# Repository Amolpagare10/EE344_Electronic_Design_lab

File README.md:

<!-- Modify from here -->
# Project Overview    

### Project Name: *EcoSync 8X* - A dsPIC33A microcontroller based ultrasonic guided wave structural health monitoring system
### Team Number: TUE-08

### Team Members:  
(in alphabetical order)
- **[Amol Pagare](https://github.com/Amolpagare10)**
- **[Angad Singh](https://github.com/lightning-starboy)**  
- **[Anuj Gautam](https://github.com/10Anuj)**  
- **[Anuj Yadav](https://github.com/anujyadav10457)**  
- **[Subhanshu Choudhary](https://github.com/Subhanshu-Leo)**

## Problem Statement and Solution

This project introduces an **embedded data acquisition system** using **ultrasonic guided wave–based structural inspection**. The system is built around an **8-channel transducer interface**, where each channel can be dynamically configured as either a **transmitter** or **receiver**, enabling flexible and reconfigurable testing setups—all controlled via a user-friendly **graphical user interface (GUI)**.This is the device [User Manual.](others/USER_MANUAL.pdf)

---

### Key Features:

- **Signal Generation**: Produces a 100 kHz, 5-cycle Hanning-windowed pulse with a 10 V<sub>pp</sub> amplitude, which can be amplified up to 100 V<sub>pp</sub> using an external power amplifier.
- **Receiver Signal**: Includes high-fidelity signal acquisition with instrumentation amplifiers for accurate and noise-reduced signal capture.
- **Channel Multiplexing**: Supports 8-channel multiplexing for dynamic selection of transmitter and receiver transducers.
- **Wireless Communication**: Enables real-time data transmission to a host computer for visualization and offline analysis.
- **Structural Health Monitoring**: Ideal for applications in pipelines, metal and composite panels, and other critical infrastructure requiring long-term monitoring and inspection.
  <!--  -->

## 1. Source Code
### Project Directory Structure

```
/Project-Root
├── /src                      # Source code folder
│   ├── /dspic33ak128MC106      # Microcontroller 1
│   │   ├── integrated.c          # Handles DAC and ADC functionality
│   │   ├── command_protocol.c    # Implements the command protocol logic
│   │   ├── protocol_def.h        # Definitions for the command protocol
│   │
│   ├── /esp32                  # Microcontroller 2
│   │   ├── wifi_code.ino         # WiFi setup and communication code
```

### Programming the Microcontrollers

For programming the **dsPIC33AK128MC106** microcontroller, we used **MPLAB X IDE** in combination with the **XC-DSC compiler**.  
For the **ESP32** module, the programming was done using the **Arduino IDE**.  
In both cases, the code was written in the **C programming language**.

---

### How to Use the Code

### 1. Install Required Tools

- **MPLAB X IDE**: The official integrated development environment provided by Microchip for developing and debugging embedded applications.
- **XC-DSC Compiler**: A compiler specifically designed for 16-bit Digital Signal Controllers (DSCs) like the dsPIC33 series.

Both tools can be downloaded from the Microchip website:  
[https://www.microchip.com/en-us/tools-resources/develop/mplab-x-ide](https://www.microchip.com/en-us/tools-resources/develop/mplab-x-ide)

---

### 2. Creating a New Project in MPLAB X IDE

Once the tools are installed, follow these steps to create and configure a new project for the dsPIC33AK128MC106:

1. **Launch MPLAB X IDE**.
2. Go to the **File** menu and select **New Project**.
3. In the project wizard:
    - Select **Microchip Embedded** under **Categories**
    - Select **Application Projects** under **Projects**  
      
4. Click **Next**, then:
    - Choose **16-bit DSCs (dsPIC33)** from the **Family** dropdown
    - Select **dsPIC33AK128MC106** from the list of devices  
      
5. Click **Next**, then choose the **XC-DSC** compiler from the list of available compilers  
   
6. Provide a name for your project and choose a directory where it will be saved  

---

### 3. Adding Source Code Files

Once your project is set up:

1. In the **Projects** tab within MPLAB X IDE, navigate to the `Source Files` folder.
2. Copy and paste the provided `.c` and `.h` files into the `Source Files` directory.  

---

### 4. Building and Programming the Device

To compile and upload your code:

1. Click on the **Build Project** button (hammer icon) in the toolbar to compile the code.  
   
2. After a successful build, click the **Make and Program Device** button (downward arrow icon) to upload the code to the microcontroller.  
   
3. Once the microcontroller is programmed successfully, the onboard **status LED** should start blinking, indicating that the code is running.

---

## 2. PCB Design
```
/Project-Root
├──pcb/
|  ├── pictures/                         # Existing folder
|  ├── 1N914.zip                         # Diode library
|  ├── LIB_23LCV04M-I_ST.zip            # Official library
|  ├── LIB_DAC7821IPWR.zip              # Official DAC library
|  ├── MAX1426EAI_.zip                  # ADC or other component library
|  ├── Readme.md                        # Main documentation or instructions
|  ├── design.kicad_pcb                 # KiCAD PCB layout
|  ├── design.kicad_pro                 # KiCAD project file
|  ├── design.kicad_sch                 # KiCAD schematic file
|  ├── ul_DAC7821IPW.zip                # User-provided DAC library
|  ├── ul_INA128U.zip                   # User-provided instrumentation amp
|  ├── ul_TL072CP.zip                   # User-provided op-amp library
```
We've made our PCB using KiCAD software and these are the footprints used in the PCB design.

## 3. Laser Cut Panels
### Enclosure Design and Fabrication

The enclosure for our project was custom-designed and fabricated using **laser cutting**. All design files are located in the `/3d_models` directory. The box design was created using **Autodesk Fusion 360** and exported as a **DXF file** suitable for laser cutting.
```
/Project-Root
├── /3d_models              # 3D models and laser cut files
│   ├── box_model.dxf         # DXF file with all 6 faces for laser cutting
│   ├── Box_CAD_Sketch.png    # Sketch preview of the box design
```

### Box Details

- The enclosure consists of **six interlocking acrylic panels**, each precisely designed with **notches** that fit into complementary notches on adjacent panels for seamless assembly.
- Panels are cut from **5 mm thick acrylic sheets**.
- The box is assembled using **hot glue**, which securely holds the panels together.

---

### Custom Cutouts

- **Back Panel**:
  - Includes a cutout for the **power supply**.
- **Side Panel**:
  - It has a cutout specifically for the **dsPIC33AK128MC106 microcontroller board**.
  - Below the microcontroller cutout, there are **eight holes** for the **transducer connectors**, allowing easy interfacing with the external sensors.

## 4. Bill Of Materials  
This project involves various electronic components including microcontrollers, converters, sensors, and support modules, sourced from vendors like DigiKey, Robu, Mouser, and Microchip.

### Component Overview

| **Category**               | **Component**                             | **Quantity** | **Vendor**              | **Cost (INR)** |
|---------------------------|-------------------------------------------|--------------|--------------------------|----------------|
| **Microcontrollers & Dev Boards** | ESP32 WiFi Module, DIM Module, Development Board | 3            | DigiKey, Microchip       | ₹9,457.00      |
| **Signal Conversion**     | DAC, ADC, INA128                          | 3            | Mouser, DigiKey, Robu    | ₹1,910.00      |
| **Power Modules**         | SMPS (x2), Buck & Boost Converters       | 5            | DigiKey, Robu            | ₹4,420.00      |
| **Sensors**               | PZT Sensor (SP-5H)                        | 8            | CPS Lab                  | ₹40,000.00     |
| **Misc ICs**              | MUX, Electronic Switch, Opamp            | 3            | Mouser, DigiKey, Robu    | ₹2,675.00      |
| **Mechanical**            | Acrylic Sheet Panels (Laser Cut)         | 6            | WEL                      | NA             |

---

### **Total Cost**: ₹58,462.00

> Note: Cost for acrylic sheets not included.

## **Learning, Experiences, Hardships, and Difficulties Encountered**

<!-- This course has been a valuable learning experience for us. It taught us how to transform an idea into a tangible product, which was both challenging and exciting. Throughout the project, we experienced highs when things were progressing smoothly, when our DAC wasn't giveing the correct waveform, as well as lows when nothing seemed to work despite our efforts, when our ADC couldnt't work reliably. There were moments of frustration, especially when technical setbacks slowed us down or when not all team members could contribute equally due to other academic commitments, even when we had quizes and exam, we tried to invest some time according to our free timings. In hindsight, we believe a more effective distribution of tasks could have helped us manage these challenges better. Nonetheless, the journey was immensely enriching, and we’re grateful for the opportunity to learn and grow through this experience. -->

This course has been a valuable learning experience for us. It taught us how to transform an idea into a tangible product, which was both challenging and exciting. 

Throughout the project, we experienced several highs—such as when things were progressing smoothly—and lows, like when our DAC wasn't giving the correct waveform or when our ADC couldn’t work reliably. 

There were moments of frustration, especially when technical setbacks slowed us down or when not all team members could contribute equally due to other academic commitments. Even during quizzes and exams, we tried to invest time according to our free schedules.

In hindsight, we believe a more effective distribution of tasks could have helped us manage these challenges better. Nonetheless, the journey was immensely enriching, and we’re grateful for the opportunity to learn and grow through this experience.

## Current status and Future Prospects for our Project

---

### 1. Partially Incomplete ADC

#### What Was Done:
- Tested the ADC on the PCB using waveform inputs from the INA.
- Output signal remained constant across tests.
- Tried using an earlier-working ADC on a breadboard—still observed a constant output.

#### Unresolved Issues:
The root cause remains unidentified. Potential issues could include:
- Incorrect voltage reference.
- INA output entering saturation.
- Firmware misconfiguration.
- Inaccurate or missing clock signals.

#### Parts Not Completed:
- Full integration of the ADC into the signal chain.
- Validation using real digitized sensor data.
- Establishing a complete end-to-end data acquisition pipeline for signal processing.

---

### 2. Partially Incomplete Wi-Fi Module Interface

#### What Was Done:
- Attempted UART-based interfacing of the Wi-Fi module with the Curiosity board.
- Identified that the UART pins on the board were non-functional.

#### Progress Made:
- Successfully interfaced the Wi-Fi module with a GUI.
- Enabled both data transmission and reception.
- Initially received garbage data when connected to a laptop, resolved by:
  - Splitting the code into two modules:
    - One for the Wi-Fi module at **115200 baud rate**.
    - One for laptop communication at **9600 baud rate**.

#### Parts Not Completed:
- Wi-Fi integration with the Curiosity board.
- Wireless transmission of sensor data from the MCU.
- Real-time wireless data logging and remote visualization.

---

## Future Prospects

### 1. Enhanced GUI Interface
- Develop a more intuitive and interactive GUI.
- Key features to include:
  - Real-time waveform plotting.
  - Diagnostic alerts for system anomalies.
  - Interactive signal control and parameter tuning.

### 2. DI Map Algorithm Improvements
- Optimize the **Damage Index (DI)** mapping algorithm for better defect localization and embedded performance.
- Add a validation metric to evaluate and improve accuracy.
- Enable dynamic updates on the GUI for visual feedback.

### 3. Complete Wi-Fi Module Integration
- Finalize integration of the Wi-Fi module with the Curiosity board.
- Support seamless, real-time wireless data transmission.
- Enable remote monitoring through a web interface or mobile application.

### 4. SRAM-Based Memory Expansion
- Integrate external **SRAM** to overcome microcontroller memory limitations.
- Support:
  - High-resolution signal logging.
  - Buffered data acquisition.
  - Advanced signal processing tasks on-device.

---

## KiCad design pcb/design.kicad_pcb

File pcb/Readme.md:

# PCB Design Issues:

- Our SMD INA on the PCB was not working. We replaced it with another SMD INA, but it still didn't work. Since we didn’t have any more SMD INAs, we used a DIP INA on a breadboard and connected it to the PCB — and it started working.

- In the ADC, we grounded the CMLP pin (pin 11), as the datasheet mentioned that for DC coupling, it should be grounded. However, during breadboard testing, we found that it worked when connected to 5V instead.

- Even after all this, the ADC on the PCB is still not working. We tried to figure out the issue by checking if the clock is working, if we are receiving data at the ADC, and if the power supply to the ADC is correct. We found that everything appears to be in order, yet we are still not receiving any data from the ADC.

# Purpose of the PCB:

- In our project, almost everything relied on the PCB. We had to use components like the DAC, TL072, power amplifier, electronic switch, multiplexer, INA, and ADC — all of which required reliable and organized connections. Using a PCB was the best choice to ensure clean and consistent wiring.

- Moreover, we found that small mistakes on the breadboard made debugging very cumbersome. In contrast, the PCB allowed us to make all the connections properly and verify them once. After the PCB arrived and we tested it, we could trust the setup and focus on the actual performance of the circuit.

# Explanation of PCB connections 

- Our microcontroller was connected to the DAC to convert digital data into analog signals. The signal was then passed through a TL072 and a power amplifier to amplify it. Next, an electronic switch was used to select which transducer would transmit the signal.

- After transmission, a multiplexer (MUX) was used to select the transducer that would receive the signal. The received signal was then passed through an INA and a clipper — the INA amplified the signal, while the clipper limited high voltages to protect the circuit.

- Finally, the processed analog signal was fed into an ADC to convert it back into digital form, which was then sent to the PC for post-processing.

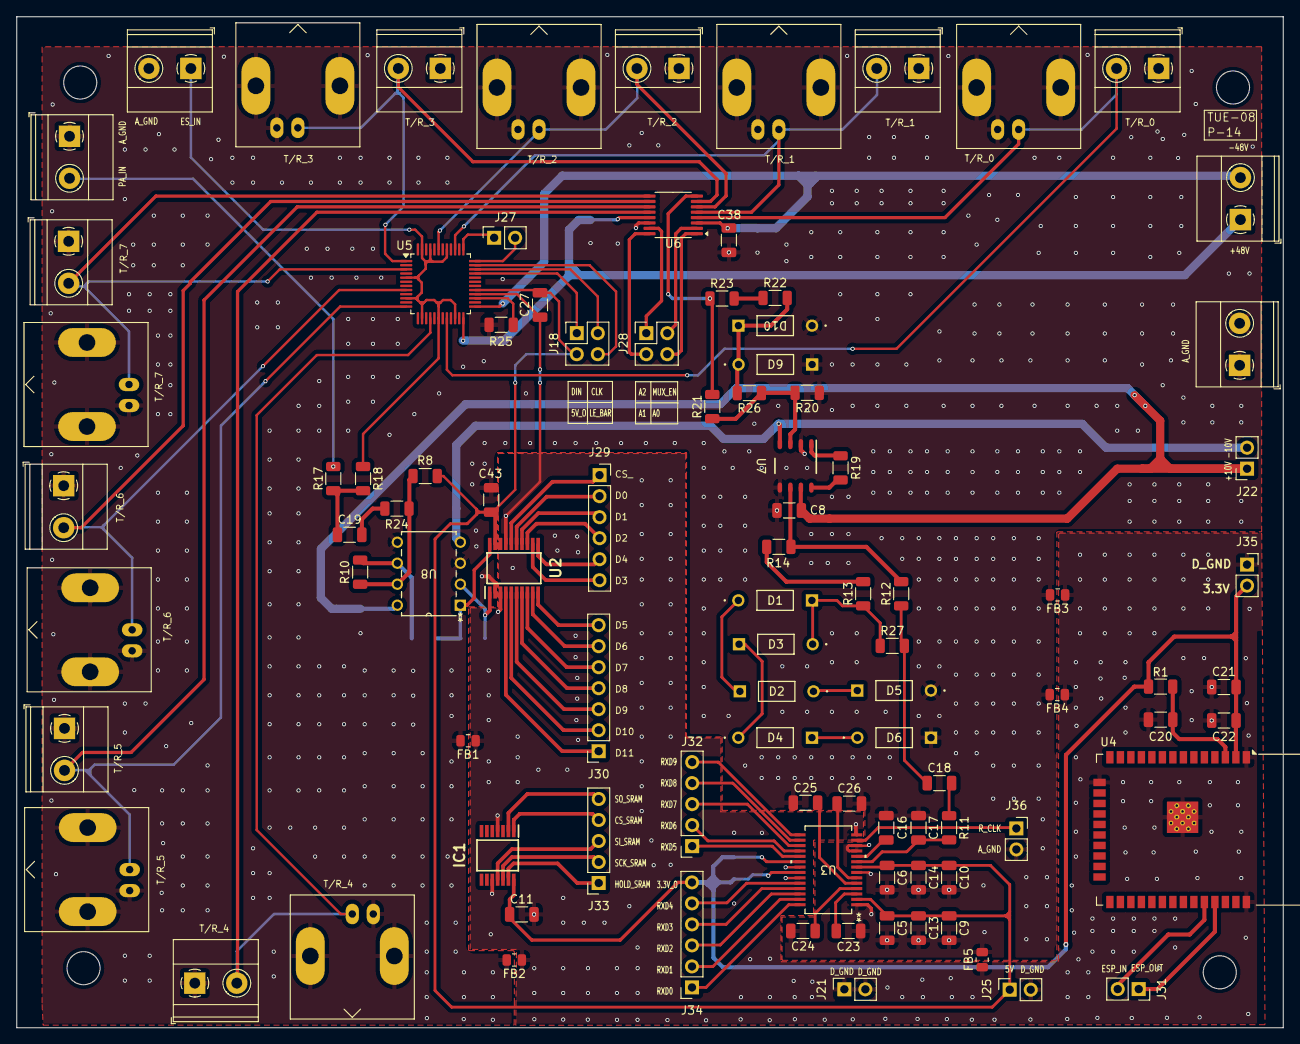
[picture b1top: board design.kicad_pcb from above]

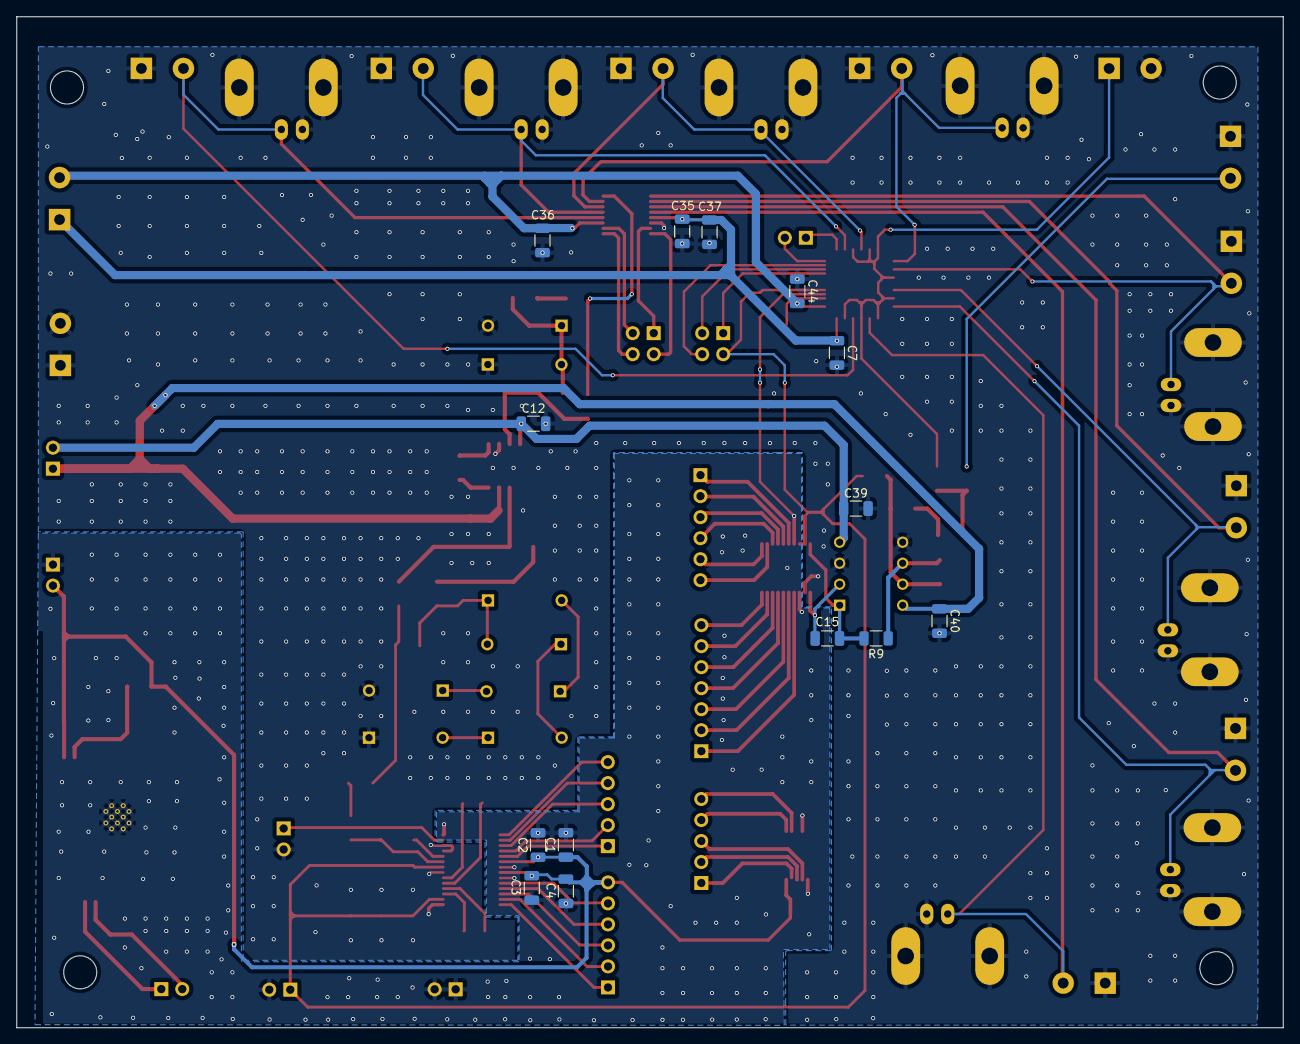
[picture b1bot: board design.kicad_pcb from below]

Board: 2 copper layers, 153.2 x 122.3 mm, 109 parts (14 on the bottom side), 87 nets.

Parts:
A_GND: Screw_Terminal_01x02; TerminalBlock_Phoenix_MKDS-1,5-2-5.08_1x02_P5.08mm_Horizont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
C1, C3, C13, C14: 2.2uf; C_1206_3216Metric
C2, C4, C8, C9, C10, C11, C12, C16, C18, C19, C23, C24, C25, C26, C27, C39, C40, C43, C44: 0.1uf; C_1206_3216Metric
C5, C6: 100pf; C_1206_3216Metric
C7, C37, C38: 0.1u; C_1206_3216Metric
C15: C; C_1206_3216Metric
C17: 22fp; C_1206_3216Metric
C20, C22: 0.1uF; C_1206_3216Metric
C21: 10uF; C_1206_3216Metric
C35, C36: 1u; C_1206_3216Metric
D1, D2, D3, D4, D5, D6, D9, D10: D; 1n914
FB1, FB2, FB3, FB4, FB5: FerriteBead; R_0805_2012Metric
IC1: 23LCV04M-I_ST; SOP65P640X120-14N
J2, J3, J4, J5, J6, J7, J8, J9: Conn_Coaxial; BNC_Amphenol_B6252HB-NPP3G-50_Horizontal
J10, J11, J12, J13, J14, J15, J16, J17, J19, J20, J23: Screw_Terminal_01x02; TerminalBlock_Phoenix_MKDS-1,5-2-5.08_1x02_P5.08mm_Horizont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
J18, J28: Conn_02x02_Top_Bottom; PinSocket_2x02_P2.54mm_Vertical
J21, J22, J25, J27, J31, J35, J36: Conn_01x02; PinSocket_1x02_P2.54mm_Vertical
J29, J34: Conn_01x06; PinSocket_1x06_P2.54mm_Vertical
J30: Conn_01x07; PinSocket_1x07_P2.54mm_Vertical
J32, J33: Conn_01x05; PinSocket_1x05_P2.54mm_Vertical
R1, R8, R10, R20: 10k; R_1206_3216Metric
R9: 5k; R_1206_3216Metric
R11: 50; R_1206_3216Metric
R12, R14, R17, R18, R21, R23, R25, R26, R27: 0; R_1206_3216Metric
R13, R19, R22: 100; R_1206_3216Metric
R24: 180; R_1206_3216Metric
U2: DAC7821IPWR; SOP65P640X120-20N
U3: MAX1426EAI+; adc
U4: ESP32-WROOM-32DM113DH6400PH3Q0; ESP32-WROOM-32D
U5: HV232FG-G; LQFP-48_7x7mm_P0.5mm
U6: TMUX8108PWR; TSSOP-16_4.4x5mm_P0.65mm
U7: INA128PA; ina128
U8: TL072CP; tl072

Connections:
+3.3V: C1.1, C2.1, C3.1, C4.1, C11.1, C21.2, C22.2, IC1.14 (VCC), J34.6, J35.2, R1.2, U3.20 (DVDD), U3.22 (DVDD), U4.2 (3V3)
+5V: C5.1, C6.1, C9.1, C10.1, C13.1, C14.1, C27.2, C43.2, J18.2, J25.1, R8.1, U2.18 (VDD), U2.19 (VREF), U3.2 (AVDD), U3.8 (AVDD), U5.29 (VDD)
+10V: C8.2, C40.1, J22.1, U7.7 (V+), U8.8 (VCC+)
+48V: C7.1, C35.1, C37.1, J23.1, U5.24 (VPP), U6.13 (VDD)
-10V: C12.1, C39.1, J22.2, U7.4 (V-), U8.4 (VCC-)
-48V: C36.2, C38.2, C44.2, J23.2, U5.25 (VNN), U6.3 (VSS)
A0: J28.4, U6.1 (A0)
A1: J28.2, U6.16 (A1)
A2: J28.1, U6.15 (A2)
A_GND: A_GND.1, C5.2, C6.2, C7.2, C8.1, C9.2, C10.2, C12.2, C13.2, C14.2, C16.1, C17.2, C23.2, C24.2, C25.2, C26.2, C35.2, C36.1, C37.2, C38.1, C39.2, C40.2, C43.1, C44.1, D5.1 (K), D6.2 (A), D9.2 (A), D10.1 (K), FB1.2, FB2.2, FB3.2, FB4.2, FB5.2, J2.2 (Ext), J3.2 (Ext), J4.2 (Ext), J5.2 (Ext), J6.2 (Ext), J7.2 (Ext), J8.2 (Ext), J9.2 (Ext), J10.1, J11.1, J12.1, J13.1, J14.1, J15.1, J16.1, J17.1, J19.1, J19.2, J20.2, J36.2, R20.1, R25.2, U2.2 (IOUT2), U3.1 (AGND), U3.7 (AGND), U3.11 (CMLP), U3.12 (CMLN), U6.14 (GND), U7.2 (V-IN), U7.5 (REF), U8.3 (1IN+), U8.5 (2IN+)
CLK: J18.3, U5.34 (CLK)
CLR: J27.2, U5.36 (CLR)
CS_: J29.1, U2.16 (CS_N)
CS_SRAM: IC1.1 (~CS), J33.4
D0: J29.2, U2.15 (DB0_LSB)
D1: J29.3, U2.14 (DB1)
D2: J29.4, U2.13 (DB2)
D3: J29.6, U2.12 (DB3)
D4: J29.5, U2.11 (DB4)
D5: J30.7, U2.10 (DB5)
D6: J30.6, U2.9 (DB6)
D7: J30.5, U2.8 (DB7)
D8: J30.4, U2.7 (DB8)
D9: J30.3, U2.6 (DB9)
D10: J30.2, U2.5 (DB10)
D11: J30.1, U2.4 (DB11_MSB)
DAC_OUT: C19.1, R17.2, R18.2
DIN: J18.1, U5.33 (DIN)
DOUT: J27.1, U5.37 (DOUT)
D_GND: C1.2, C2.2, C3.2, C4.2, C11.2, C20.1, C21.1, C22.1, C27.1, FB1.1, FB2.1, FB3.1, FB4.1, FB5.1, IC1.4 (VSS), IC1.10 (VBAT), J21.1, J21.2, J25.2, J35.1, U2.3 (GND), U2.17 (R_W_N), U3.14 (*OE/PD), U3.21 (DGND), U3.23 (DGND), U4.1 (GND), U4.15 (GND), U4.38 (GND), U4.39 (GND), U5.28 (GND)
ESP_DATA_IN: J31.2, U4.34 (RXD0)
ESP_DATA_OUT: J31.1, U4.35 (TXD0)
ES_IN: J20.1, R18.1, U5.5 (SW4), U5.10 (SW3), U5.14 (SW2), U5.18 (SW1), U5.22 (SW0), U5.41 (SW7), U5.45 (SW6), U5.47 (SW5)
HOLD_SRAM: IC1.13 (~HOLD/SIO3), J33.1
INA_OUT: C18.1, R12.1, R27.2
INN: C16.2, U3.10 (INN)
INP: C17.1, R11.2, U3.9 (INP)
LE_BAR: J18.4, U5.35 (*LE)
MUX_EN: J28.3, U6.2 (EN)
MUX_OUT: R21.2, R23.2, U6.8 (D)
unnamed: C18.2, R11.1
unnamed: C19.2, R24.2
unnamed: D1.2 (A), D3.1 (K), R13.1, R27.1
unnamed: D1.1 (K), D2.2 (A)
unnamed: D2.1 (K), D5.2 (A)
unnamed: D3.2 (A), D4.1 (K)
unnamed: D4.2 (A), D6.1 (K)
unnamed: D9.1 (K), D10.2 (A), R22.2, R26.2
unnamed: R13.2, R14.1
unnamed: R19.1, U7.1 (RG)
unnamed: R19.2, U7.8 (RG)
unnamed: R22.1, R23.1
unnamed: C15.2, U2.1 (IOUT1), U8.2 (1IN-)
unnamed: C15.1, R9.1, U2.20 (RFB), U8.1 (1OUT)
unnamed: C20.2, R1.1, U4.3 (EN)
unnamed: R25.1, U5.27 (RGND)
unnamed: R20.2, R21.1, R26.1, U7.3 (V+IN)
unnamed: R12.2, R14.2, U7.6 (VO)
unnamed: R9.2, R10.1, U8.6 (2IN-)
unnamed: R8.2, R10.2, R24.1, U8.7 (2OUT)
PA_IN: A_GND.2, R17.1
RXD0: J34.1, U3.28 (D0)
RXD1: J34.2, U3.27 (D1)
RXD2: J34.3, U3.26 (D2)
RXD3: J34.4, U3.25 (D3)
RXD4: J34.5, U3.24 (D4)
RXD5: J32.1, U3.19 (D5)
RXD6: J32.2, U3.18 (D6)
RXD7: J32.3, U3.17 (D7)
RXD8: J32.4, U3.16 (D8)
RXD9: J32.5, U3.15 (D9)
R_CLK: J36.1, U3.13 (CLK)
R_CML: C26.1, U3.6 (CML)
R_REFIN: C24.1, U3.4 (REFIN)
R_REFN: C25.1, U3.5 (REFN)
R_REFP: C23.1, U3.3 (REFP)
SCK_SRAM: IC1.12 (SCK), J33.2
SI_SRAM: IC1.11 (SI/SIO0), J33.3
SO_SRAM: IC1.2 (SO/SIO1), J33.5
T/R_0: J2.1 (In), J10.2, U5.20 (SW0), U6.4 (S1)
T/R_1: J3.1 (In), J11.2, U5.39 (SW7), U6.5 (S2)
T/R_2: J4.1 (In), J12.2, U5.43 (SW6), U6.6 (S3)
T/R_3: J5.1 (In), J13.2, U5.1 (SW5), U6.7 (S4)
T/R_4: J6.1 (In), J14.2, U5.16 (SW1), U6.12 (S5)
T/R_5: J7.1 (In), J15.2, U5.12 (SW2), U6.11 (S6)
T/R_6: J8.1 (In), J16.2, U5.8 (SW3), U6.10 (S7)
T/R_7: J9.1 (In), J17.2, U5.3 (SW4), U6.9 (S8)

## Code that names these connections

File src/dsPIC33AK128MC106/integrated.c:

#include <xc.h>                         // Include processor header
#include <stdio.h>                      // For printf and snprintf
#include <stdint.h>                     // For uint types
#include <stdlib.h>                     // For standard utilities
#define FCY 100000000UL                 // Define instruction cycle frequency (Fosc/2 = 200MHz / 2)
#include <libpic30.h>                   // For __delay_us and other helpers
#include <math.h>                       // Math operations
#include "mcc_generated_files/system/clock.h"  // Clock initialization
#include "protocol_def.h"                      // For cmd protocol
// Define ports for DAC and multiplexer
#define DATA_PORT LATA        
#define DATA_TRIS TRISA       

// Define control lines for 3-bit multiplexer
#define MUX_A0 LATAbits.LATA9
#define MUX_A1 LATAbits.LATA10
#define MUX_A2 LATAbits.LATA2
#define MUX_EN LATAbits.LATA3

// Define DAC chip select and data lines
#define DAC_CSn LATDbits.LATD12
#define DAC_data LATD

// Define ADC data and clock lines
#define ADC_data LATC
#define ADC_clk LATAbits.LATA4

// Define Chip Select line for digital logic
#define CS_TRIS  TRISCbits.TRISC0
#define CS_LAT  LATCbits.LATC0
    
#define BAUDRATE 9600                   // UART baudrate
#define BRGVAL (((FCY / BAUDRATE) / 16) - 1)  // Calculate UART baud rate register value

// Define shift register connections (Edge Sequencer)
#define ES_DIN LATAbits.LATA8
#define ES_CLK LATAbits.LATA11
#define ES_LEn LATAbits.LATA1
#define ES_CLR LATAbits.LATA7
#define ES_DOUT LATAbits.LATA0

// UART receiver initialization
void uart_rx_init() {
    _U1RXR = 59;                        // Map RX to RP59
    U1CONbits.MODE = 0;                // 8-bit UART, asynchronous mode
    U1CONbits.BRGS = 0;                // Low speed baud
    U1CONbits.CLKSEL = 0;              // Use system clock/2
    U1CONbits.STP = 0;                 // 1 stop bit
    U1BRG = BRGVAL;                    // Set baud rate
    U1CONbits.ON = 1;                  // Enable UART module
    U1CONbits.RXEN = 1;                // Enable RX
}

// UART transmitter initialization
void uart_tx_init() {
    _RP58R = 9;                        // Map TX to RP58
    U1CONbits.TXEN = 1;               // Enable TX
}

// Transmit a single character over UART
void uart_transmit_char(char c) {
    while (U1STATbits.UTXBF);         // Wait if TX buffer full
    U1TXB = c;                         // Load character to TX buffer
}

// Transmit a null-terminated string over UART
void uart_transmit_string(const char *str) {
    while (*str) {
        uart_transmit_char(*str++);   // Send each character
    }
}

// Transmit an integer as a string
void uart_transmit_no(const uint16_t data) {
    char buffer[20];
    snprintf(buffer, sizeof(buffer), "%d", data);  // Convert to string
    uart_transmit_string(buffer);                  // Send string
}

// Hanning window (50 points)
const uint16_t hanningTable[50] = {
    0x800,0x812,0x842,0x872,0x867,0x7EF,0x718,0x641,0x5F9,0x6B1,
    0x867,0xA87,0xC12,0xC17,0xA36,0x6F0,0x38F,0x19E,0x233,0x554,
    0x9E1,0xDF8,0xFCF,0xE81,0xA85,0x57B,0x17F,0x031,0x208,0x61F,
    0xAAC,0xDCD,0xE62,0xC71,0x910,0x5CA,0x3E9,0x3EE,0x579,0x799,
    0x94F,0xA07,0x9BF,0x8E8,0x811,0x799,0x78E,0x7BE,0x7EE,0x800
};

// Sine wave (20 points)
const uint16_t sineTable[20] = {
    0x7fd, 0x814, 0x829, 0x83a, 0x844, 0x848, 0x844, 0x83a,
    0x829, 0x814, 0x7fd, 0x7e6, 0x7d1, 0x7c0, 0x7b6, 0x7b2,
    0x7b6, 0x7c0, 0x7d1, 0x7e6
};

// Function declarations
void DAC_init(void);
void DAC_write(uint16_t data);
void DAC_Controller(uint16_t amplitude);
void Timer1_Init(void);

volatile uint16_t cnt = 0;              // Toggle counter for DAC waveform
volatile uint16_t amplitude = 0xFFFF;   // Default amplitude

// Write 12-bit data to DAC
void DAC_write(uint16_t data) {
    DATA_PORT = (DATA_PORT & 0xF000) | (data & 0x0FFF);  // Mask upper bits
    __delay_us(1);
    CS_LAT = 0;             // Pull chip select low
    __delay_us(1);
    CS_LAT = 1;             // Pull chip select high
    __delay_us(1);
}

// Generate waveform using DAC
void DAC_Controller(uint16_t amplitude) {
    uint16_t normalized_value = (uint16_t)(((uint32_t)amplitude * 4095) / 65536);  // Scale to 12-bit
    uint16_t Data;

    if (cnt) {
        Data = normalized_value;
        __delay_us(1);
    }
    else {
        Data = 0;
        __delay_us(1);
    }
    cnt ^= 1;               // Toggle cnt
    DAC_write(Data);        // Send to DAC
}

// Initialize multiplexer control lines
void TMUX_init(){
    TRISAbits.TRISA9 =  0;
    TRISAbits.TRISA10 = 0;
    TRISAbits.TRISA2 =  0;
    TRISAbits.TRISA3 =  0; 
}

// Initialize DAC
void DAC_init(){
    TRISD = 0;              // Set PORTD as output
    DAC_CSn = 0;            // Enable DAC chip
}

// Control 3-bit address of multiplexer
void TMUX_Control(uint8_t address) {
    MUX_A0 = address & 0x01;
    MUX_A1 = (address & 0x02)>>1;
    MUX_A2 = (address & 0x04)>>2;
}

// Initialize ADC input and clock
void ADC_init(){
    TRISC = 0xFFF;          // Set PORTC as input
    TRISAbits.TRISA4 = 0;   // Set clock pin as output
    ADC_clk = 0;            // Initialize clock low
}

// Initialize edge sequencer shift register
void ES_init(){
    TRISAbits.TRISA8 = 0;   // DIN
    TRISAbits.TRISA11 = 0;  // CLK
    TRISAbits.TRISA1 = 0;   // LE
    TRISAbits.TRISA7 = 0;   // CLR
    TRISAbits.TRISA0 = 1;   // DOUT as input

    ES_LEn = 1;             // Disable latch
    ES_CLK = 0;
    ES_CLR = 0;             // Clear shift register
    __delay_us(1);
    ES_CLR = 1;             // Stop clearing
    __delay_us(1);
    ES_CLR = 0;             // Reassert
}

int main(void) {
    CLOCK_Initialize();     // Initialize system clock
    DAC_init();             // Initialize DAC
    TMUX_init();            // Initialize multiplexer
    MUX_EN = 1;             // Enable multiplexer
    TMUX_Control(MUX_data);        // Set MUX to channel 0
    ADC_init();             // Initialize ADC
    ES_init();              // Initialize edge sequencer

    uart_rx_init();         // Init UART RX
    uart_tx_init();         // Init UART TX

    // Edge sequencer bit pattern
    uint8_t es_seq[8];
    for(int i=0;i<8;i++){
    es_seq[i] = ES_data[i];}
    //uint8_t es_seq[8] = {0,1,0,0,0,0,0,0};  // Order of channels
    ES_LEn = 0;              // Enable shift register load
    __delay_us(10);
    for (int i = 0; i < 8; i++) {
        ES_DIN = es_seq[i];                 // Load bit
        __delay_us(10);
        ES_CLK = !ES_CLK;                   // Clock pulse high
        __delay_us(10);
        ES_CLK = !ES_CLK;                   // Clock pulse low
    }
    __delay_us(10);
    ES_LEn = 1;                             // Latch the sequence

    uint16_t recvd[400];                   // Store ADC values

    while(1){
        for (int i = 0; i < 50; i++) {
            DAC_data = hanningTable[i % 50] & 0x0fff; // Set DAC data
            __delay_us(1);
            DAC_CSn = !DAC_CSn;            // Toggle chip select
            DAC_CSn = !DAC_CSn;            // Toggle again

            ADC_clk = !ADC_clk;            // Toggle ADC clock
            // Read 10-bit ADC value from specific pins
            recvd[i] = (PORTCbits.RC11 << 9 | PORTCbits.RC10 << 8 | 
                        PORTCbits.RC8 << 7 | PORTCbits.RC7 << 6 |
                        PORTCbits.RC6 << 5 | PORTCbits.RC5 << 4 |
                        PORTCbits.RC4 << 3 | PORTCbits.RC3 << 2 |
                        PORTCbits.RC2 << 1 | PORTCbits.RC0) & 0x03ff;
        }
        __delay_us(50000);  // Delay for observation
    }

    for (int i = 50; i < 400; i++) {
        ADC_clk = !ADC_clk;            // Toggle ADC clock
        // Continue reading remaining ADC values
        recvd[i] = (PORTCbits.RC11 << 9 | PORTCbits.RC10 << 8 |
                    PORTCbits.RC8 << 7 | PORTCbits.RC7 << 6 |
                    PORTCbits.RC6 << 5 | PORTCbits.RC5 << 4 |
                    PORTCbits.RC4 << 3 | PORTCbits.RC3 << 2 |
                    PORTCbits.RC2 << 1 | PORTCbits.RC0) & 0x03ff;
    }

    // Transmit alternate ADC values over UART
    for (int i = 1; i < 400; i += 2) {
        uart_transmit_no(recvd[i]);
        uart_transmit_string(",");
    }

    while (1);  // Infinite loop
}

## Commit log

2025-04-19 uploading final github repo
